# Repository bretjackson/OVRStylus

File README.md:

# OVR Stylus

The OVR Stylus is an open-source software/hardware design for a 3D input stylus used in virtual and augmented reality applications. With a touch pad, two input buttons, LRA-based vibrotactile haptic feedback, and Bluetooth communication, the 3D-printed prop’s light-weight design (35g) enables creative and precise interaction.

A paper describing the implementation was published at the [Workshop on Novel Input Devices and Interaction Techniques](https://sites.google.com/view/nidit) at the IEEE Virtual Reality 2020 conference. 

This repository archives the files needed to create your own OVR Stylus or to create a modified design.

## Repository Contents

* **/Case** - 3D printing files for the stylus case (.stl, Fusion 360 .f3z)
* **/Documentation** - A copy of the NIDIT paper (.pdf)
* **/Firmware** - Arduino  code used in the stylus and central device
* **/Hardware** - Eagle design files, BOM, Gerber files (.brd, .sch, etc.)
* **/VRPN** - Patch file and stylus classes to integrate with the [VRPN library](https://github.com/vrpn/vrpn)

### Hardware Manufacture

#### PCB

The hardware directory contains the design files needed to print the custom circuit board. The gerber files can be uploaded directly to manufactures (e.g. [Seeed Fusion Studio](https://www.seeedstudio.com/fusion.html)). Ordering specifications including board thickness and other properties are listed in the `PCB Specs - Ordering Info` file. The component placement list and assembly drawing can be used for pick-n-place machines if using professional assembly.

To modify the design the Autodesk Eagle design files for the schematic and board layout are also included.

#### Haptic Controller

The design uses the Fyber Labs [LRA Haptic Flex Module](https://www.tindie.com/products/fyberlabs/lra-haptic-flex-module/). A Samsung 8mm LRA motor can be purchased from the same website. Solder the motor leads to the +0 and -0 through-hole pads. Connect the PWM pad to the stylus's P3 pad. The VIN, GND, SDA, and SCL pads can be connected to the respective pads on the stylus. I recommend using 28 gauge stranded wire and making the leads very short. The haptic flex module is placed vertically at the button end of the stylus. 

#### Sliding Touch Sensor

To capture sliding touch input, a [Spectra Symbol 50mm Linear ThinPot poteniometer](https://www.amazon.com/SPECTRA-SYMBOLLINEAR-THINPOT-50-MM/dp/B005T844FU) is mounted in the groove in the top of the case. Solder leads to the potentiometer pins as described [here](https://learn.sparkfun.com/tutorials/softpot-hookup-guide/all). The 3V3 and GND leads can be kept shorter and be soldered to their respective pads on the stylus pcb near the RX and TX pads. The analog output tab's lead should be kept longer and soldered to the P4 pad at the front of the stylus (It will need to route behind the battery's JST connector). This P4 pad already contains a buildin 10kΩ resistor between the pad and ground that pulls the SoftPot's analog output signal down.

Once the soldering is complete, the potentimeter can be slide sideways into the groove in the top of the stylus case and the adhesive backing can be removed to secure it in place.

#### Battery

The case is designed to fit a [Sparkfun 110mAh Lithium ion battery](https://www.sparkfun.com/products/13853). The battery is mounted in the case underneath the PCB. The wires can either be routed to the front of the PCB and around the buttons to connect to the JST connector, or through the second large hole in the PCB.
    
### 3D Printed Case

The Case folder contains the STL files for the case. Multiple optical tracking end caps are included if multiple styluses will be made for use with the same optical tracking system.

For the prototype, the files were printed with a Makerbot Replicator 5th gen, although more professional results can be obtained with a higher quality resin printer. The prints were made with the standard settings in Makerbot Print, using support material. The top and bottom are designed to fit oriented vertically on the build platform. The support material will need to be removed with a razor blade. The button file will need to be printed twice for the two buttons.

The threading for both endcaps is ISO metric M14x2 profile. Depending on the quality of your printer, the threads may need to be cleaned up using a corresponding bolt and nut. Run the bolt a few times into the endcap to remove any extra plastic from the 3D printing.

The bottom component contains an ANSI 4-40 UNC threaded hole in the center support. This hole may also need the threads to be cleaned up using a steel bolt.

To assemble the components, mount the battery in the slot in the stylus bottom. Route the wires around the center support to the front of the stylus and the top of the board. The haptic module should sit vertically in the  space at the front. The LRA can be hot glued in the smaller slot at the front (The tabs may need to be bent slightly to clear the top of the case). The PCB can be screwed to the center support with a 1/4 inch 4-40 bolt. Place the 3D printed buttons so that they protrude from the top of the stylus, and snap the top and bottom together, making sure the buttons remain in place.  Screw on the end caps.

If the case needs to be modified, the Autodesk Fusion 360 design files are included in the Case directory.

### Software

The following section outlines the software requirements for both the stylus and the central device connected to the host computer.

#### Stylus Software

The stylus code is written for the Arduino environment. Download and install the [Arduino IDE](https://www.arduino.cc/en/Main/Software). The main stylus code is found in Firmware/Stylus.ino. To get started, open the file in the Arduino IDE.

To begin controling the LRA Haptic flex chip, you will need to install the Adafruit_DRV2605 Library. You can do that by going to the Arduino library manager under Sketch -> Include Library -> Manage Libraries... Then search for DRV2605 and find the Adafruit DRV2605 Library and click Install.

The stylus code uses the Pfod low-power Arduino Library by Mathew Ford. A tutorial for installing this software can be found [here](https://www.forward.com.au/pfod/BLE/LowPower/index.html). Below, we copy the most pertinent steps for archival purposes. 

Install [Sandeep Minstry's nRF5 library](https://github.com/sandeepmistry/arduino-nRF5):
1. Go into File → Preferences
2. Add `https://sandeepmistry.github.io/arduino-nRF5/package_nRF5_boards_index.json` as an "Additional Board Manager URL"
3. Open the Boards Manager from the Tools -> Board menu and install "Nordic Semiconductor nRF5 Boards".

Add the nRF5 Flash Softdevice tool:
1. In a terminal, cd <SKETCHBOOK>, where <SKETCHBOOK> is your Arduino Sketch folder:
OS X: ~/Documents/Arduino
Linux: ~/Arduino
Windows: ~/Documents/Arduino
2. Create the following directories: tools/nRF5FlashSoftDevice/tool/
3. Download nRF5FlashSoftDevice.jar to <SKETCHBOOK>/tools/nRF5FlashSoftDevice/tool/ (a local copy of nRF5FlashSoftDevice.jar is here)
4. Restart the Arduino IDE

Install the pfod_lp_nrf52 hardware support.
1. Download the [pfod_lp_nrf52.zip](https://www.forward.com.au/pfod/BLE/LowPower/pfod_lp_nrf52.zip) file. (A local copy can also be found in the Firmware directory.)
2. Start the Arduino IDE, Open the File → Preferences window an at the bottom find the directory where the preferences.txt file is stored. In Window's 7 you can click on that path to open the directory in the Explorer.
3. From the preferences.txt directory, open the packages sub-directory and then the sandeepmistry sub-directory which contains the hardware and tools directories.
4. Delete the hardware directory.
5. Unzip pfod_lp_nrf52.zip to the sandeepmistry directory to install the pfod low power support. This will install the modified hardware directory.
6. Close and restart the Arduino IDE.
7. Open the Tools → Board and scroll down to find the pfod low power nRF52832 boards.
8. Select the `*Redbear BLE Nano 2` board.
9. Under the Tools menu, make sure the programmer is set to `CMSIS-DAP`.

To Program the board, we use a [Particle Debugger](https://store.particle.io/products/particle-debugger). Connect the debugger's GND, SCLK, and SDIO pins to the corresponding pins at the front of the stylus PCB. If you intend to debug frequently, placing Pogo pins in a breadboard allow you to temporarly create connections with the stylus pcb easily without soldering.

Power the stylus pcb and then plug the particle debugger into a usb port on the programming computer. In the tools menu, make sure the usb is selected as the port.

Before the program can be loaded a Nordic Softdevice must be uploaded to the board. Select the `nRF52 Flash SoftDevice` option half way down the Tools menu. The project uses the S132 version 2.0.1 soft device. It is already included with the Sandeep Minstry package.

Once the flash is complete, upload the Stylus sketch onto the stylus pcb.

#### Host Central Device

Multiple BLE-supporting hardware can be used to connect with the stylus. Our implementation uses a stock [Arduino Nano 33 BLE](https://store.arduino.cc/usa/nano-33-ble) module to serve as a BLE to serial repeater. 

Load the Software:
1. Open the Boards Manager from the Tools -> Board menu and install "Arduino nRF528x Boards (Mbed OS)".
2. Select  `Arduino Nano 33 BLE` as the current board and make sure the port corresponds with the USB connection.
3. Upload the nano33_central.ino from the Firmware Directory to the Nano board.

#### VRPN

The VRPN directory contains a patch file to add the OVR Stylus files to the [VRPN library](https://github.com/vrpn/vrpn). The patch was made against commit: 3863b1e089b3070ae37e25fa4a85ab3bb138ee12

After cloning the vrpn library, apply the patch:
```
git apply vrpn_ovrstylus_changes.patch
```

The Stylus device files are also included in the VRPN directory if you would like to manually apply them.

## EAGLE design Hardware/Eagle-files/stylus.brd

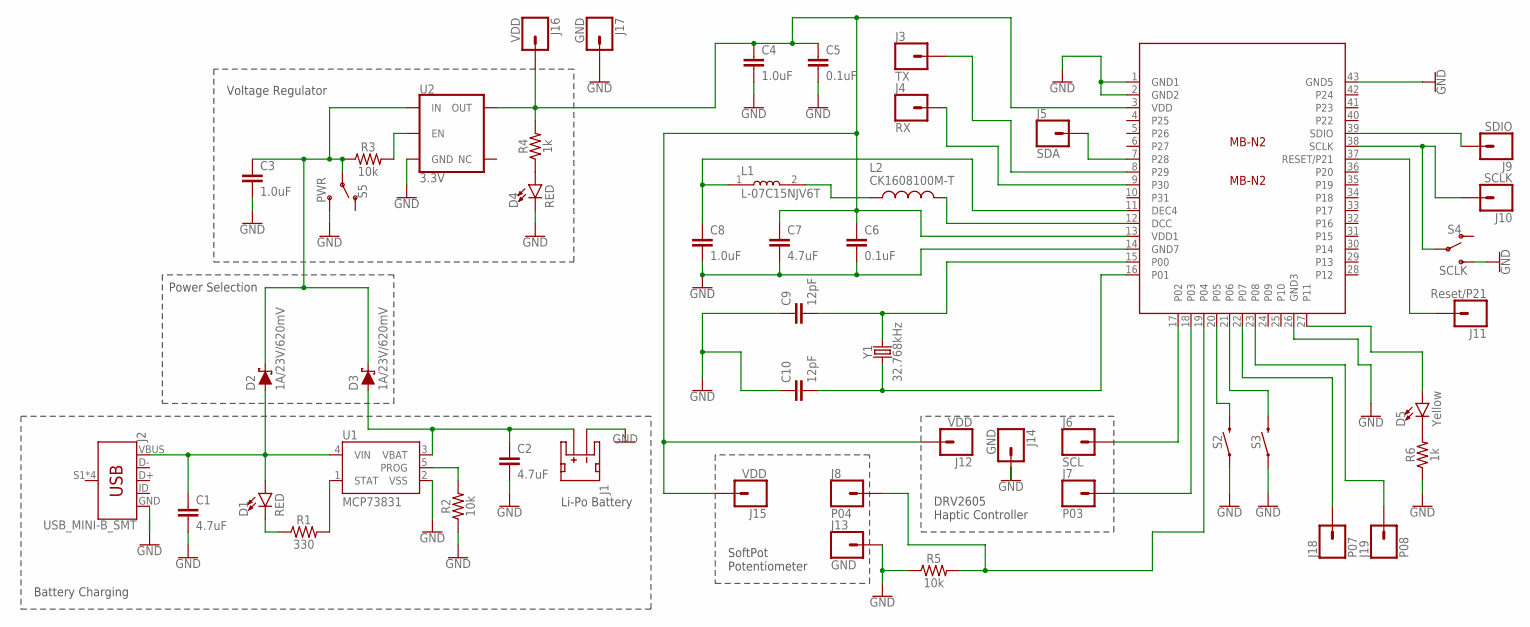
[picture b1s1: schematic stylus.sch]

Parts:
C1, C2, C7: 4.7uF; 0603
C3, C4, C8: 1.0uF; 0603
C5, C6: 0.1uF; 0603
C9, C10: 12pF; 0603
D1: RED; LED-1206
D2, D3: 1A/23V/620mV; SOD-323
D4: RED; LED-0603
D5: Yellow; LED-1206
J1: LIPO Bat; JST-2-SMD
J2: USB_MINI-B_SMT; USB-MINIB
J3: TX; 1X01
J4: RX; 1X01
J5: SDA; 1X01
J6: SCL; 1X01
J7: P03; 1X01
J8: P04; 1X01
J9: SDIO; 1X01
J10: SCLK; 1X01
J11: Reset/P21; 1X01
J12, J15, J16: VDD; 1X01
J13, J14, J17: GND; 1X01
J18: P07; 1X01
J19: P08; 1X01
L1: L-07C15NJV6T; INDC1005X60N
L2: CK1608100M-T; INDC1608X95N
MB-N2: MB-N2
R1: 330; 0603
R2, R3, R5: 10k; 0603
R4, R6: 1k; 0603
S2, S3: MOMENTARY-SWITCH-SPST-SMD-4.5MM; TACTILE_SWITCH_SMD_4.5MM
S4: SCLK; SWITCH_DPDT_SMD_AYZ0202
S5: PWR; SWITCH_SPST_SMD_A
U1: MCP73831; SOT23-5
U2: 3.3V; SOT23-5
Y1: 32.768kHz; CRYSTAL-SMD-3.2X1.5MM

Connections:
DCC: L2.2, MB-N2.12 (DCC)
DEC4: C8.1, L1.1, MB-N2.11 (DEC4)
EN: R3.2, U2.3 (EN)
GND: C1.2, C2.2, C3.2, C4.2, C5.2, C6.2, C7.2, C8.2, C9.1, C10.1, D4.C, J1.1 (-), J2.GND, J13.1, J14.1, J17.1, MB-N2.1 (GND1), MB-N2.2 (GND2), MB-N2.14 (GND7), MB-N2.26 (GND3), MB-N2.43 (GND5), R2.1, R5.1, R6.1, S2.2 (1), S2.3 (1), S3.2 (1), S3.3 (1), S4.3 (S), S5.3 (S), U1.2 (VSS), U2.2 (GND)
unnamed: D1.C, R1.1
unnamed: D4.A, R4.1
unnamed: L1.2, L2.1
unnamed: C9.2, MB-N2.15 (P00), Y1.P$2 (2)
unnamed: C10.2, MB-N2.16 (P01), Y1.P$1 (1)
unnamed: J11.1, MB-N2.37 (RESET/P21)
unnamed: D5.A, MB-N2.27 (P11)
unnamed: D5.C, R6.2
P03: J7.1, MB-N2.18 (P03)
P04: J8.1, MB-N2.19 (P04), R5.2
P05: MB-N2.20 (P05), S2.1 (2), S2.4 (2)
P06: MB-N2.21 (P06), S3.1 (2), S3.4 (2)
P07: J18.1, MB-N2.22 (P07)
P08: J19.1, MB-N2.23 (P08)
PROG: R2.2, U1.5 (PROG)
RX: J4.1, MB-N2.9 (P30)
SCL: J6.1, MB-N2.17 (P02)
SCLK: J10.1, MB-N2.38 (SCLK), S4.2
SDA: J5.1, MB-N2.7 (P28)
SDIO: J9.1, MB-N2.39 (SDIO)
STAT: R1.2, U1.1 (STAT)
TX: J3.1, MB-N2.8 (P29)
VBAT: C2.1, D3.A, J1.2 (+), U1.3 (VBAT)
VDD: C4.1, C5.1, C6.1, C7.1, J12.1, J15.1, J16.1, MB-N2.3 (VDD), MB-N2.13 (VDD1), R4.2, U2.5 (OUT)
VIN: C1.1, D1.A, D2.A, J2.VBUS, U1.4 (VIN)
VR-IN: C3.1, D2.C, D3.C, R3.1, S5.2, U2.1 (IN)

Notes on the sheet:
Power Selection
DRV2605 Haptic Controller
SoftPot Potentiometer
Li-Po Battery
Voltage Regulator
Battery Charging

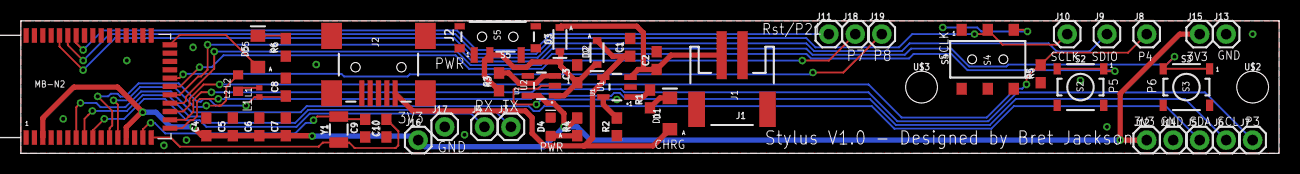
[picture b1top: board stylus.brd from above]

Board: 2 copper layers, 120.7 x 12.7 mm, 52 parts (0 on the bottom side), 30 nets.

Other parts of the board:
U$2, U$3: STAND-OFF-TIGHT

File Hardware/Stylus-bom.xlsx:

Ref Des | MP | Quantity | DIGI-KEY_PURCHASE_URL | MF | DIGI-KEY_PART_NUMBER | Description
C1, C2, C7 | CL10A475MQ8NNNC | 3 | https://www.digikey.com/product-detail/en/samsung-electro-me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 | Samsung | 1276-1907-1-ND | 4.7 µF ceramic capacitor 20% 6.3V X5R 0603
C3, C4, C8 | CL10A105KO8NNNC | 3 | https://www.digikey.com/product-detail/en/samsung-electro-me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 | Samsung | 1276-1034-1-ND | 1µF ±10% 16V Ceramic Capacitor X5R 0603
C5, C6 | CL10B104KB8NNNL | 2 | https://www.digikey.com/product-detail/en/samsung-electro-me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 | Samsung | 1276-CL10B104KB8NNNLCT-ND | 0.1µF ±10% 50V Ceramic Capacitor X7R 0603
C9, C10 | CL10C120JB8NNNC | 2 | https://www.digikey.com/product-detail/en/samsung-electro-me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 | Samsung | 1276-1254-1-ND | 12pF ±5% 50V Ceramic Capacitor C0G, NP0 0603
D1 | LTST-C150KRKT | 1 | https://www.digikey.com/product-detail/en/lite-on-inc/LTST-C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 | Lite-On Inc. | 160-1405-1-ND | LED RED CLEAR 1206 SMD
D2, D3 | BAT20JFILM | 2 | https://www.digikey.com/product-detail/en/BAT20JFILM/497-338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 | STMicroelectronics | 497-3381-1-ND | Diode Schottky 23V 1A Surface Mount SOD-323
D4 | 5988010107F | 1 | https://www.digikey.com/product-detail/en/dialight/598801010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 | Dialight | 350-2029-1-ND | LED RED CLEAR 0603 SMD
D5 | LTST-C150KSKT | 1 | https://www.digikey.com/product-detail/en/lite-on-inc/LTST-C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 | Lite-On Inc. | 160-1406-1-ND | LED YELLOW CLEAR 1206 SMD
J1 | S2B-PH-SM4-TB(LF)(SN) | 1 | https://www.digikey.com/product-detail/en/jst-sales-america-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 | JST Sales America Inc. | 455-1749-1-ND | JST CONN HEADER SMD R/A 2POS 2MM
J2 | MUSB-05-F-B-SM-A-K-TR | 1 | https://www.digikey.com/product-detail/en/samtec-inc/MUSB-05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 | Samtec Inc. | SAM13208CT-ND | USB type Mini-B Connector
L1 | L-07C15NJV6T | 1 | https://www.digikey.com/product-detail/en/johanson-technolog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 | Johanson Technology | 712-1408-1-ND | Inductor RF Chip Multi-Layer 15nH 5% 100MHz 8Q-Factor Ceramic 250mA 600mOhm DCR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
L2 | CK1608100M-T | 1 | https://www.digikey.com/product-detail/en/taiyo-yuden/CK1608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 | Taiyo Yuden | 587-1684-1-ND | INDUCTOR, 10UH, 50mA, 20%, 17MHZ, SMD
R1 | ERA-3AEB331V | 1 | https://www.digikey.com/product-detail/en/panasonic-electron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 | Panasonic | P330DBCT-ND | 330 Ohms ±0.1% 0.1W, 1/10W Chip Resistor 0603
R2, R3, R5 | RR0816P-103-D | 3 | https://www.digikey.com/product-detail/en/susumu/RR0816P-103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 | Susumu | RR08P10.0KDCT-ND | 10 kOhms ±0.5% 0.063W, 1/16W Chip Resistor 0603
R4, R6 | RR0816P-102-D | 2 | https://www.digikey.com/product-detail/en/susumu/RR0816P-102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 | Susumu | RR08P1.0KDCT-ND | 1 kOhms ±0.5% 0.063W, 1/16W Chip Resistor 0603
S2, S3 | TL3315NF160Q | 2 | https://www.digikey.com/product-detail/en/e-switch/TL3315NF1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 | E-Switch | EG4621CT-ND | Momentary Switch (Pushbutton) - SPST 4.5mm
S4 | AYZ0202AGRLC | 1 | https://www.digikey.com/product-detail/en/c-k/AYZ0202AGRLC/4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 | C&K | 401-2013-1-ND | Double Pole, Double Throw (DPDT) Switch
S5 | MA12RTR | 1 | https://www.digikey.com/product-detail/en/apem-inc/MA12RTR/6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 | APEM Inc. | 679-1847-1-ND | SWITCH SLIDE SPDT 300MA 4V Right Angle
MB-N2 | MB-N2 | 1 | CUSTOMER SUPPLIED | RedBearLab/Particle | CUSTOMER SUPPLIED | Redbearlab MB-N2 ble microcontroller
U1 | MCP73831T-2ATI/OT | 1 | https://www.digikey.com/product-detail/en/microchip-technolo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 | Microchip Technology | MCP73831T-2ATI/OTCT-ND | MCP73831T Li-Ion, Li-Pol Controller
U2 | AP2112K-3.3TRG1 | 1 | https://www.digikey.com/product-detail/en/diodes-incorporate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 | Diodes Incorporated | AP2112K-3.3TRG1DICT-ND | AP2112 - 600mA CMOS LDO Regulator w/ Enable
Y1 | SC32S-12.5PF20PPM | 1 | https://www.digikey.com/product-detail/en/seiko-instruments/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 | Seiko Instruments | 728-1073-1-ND | 32.768kHz ±20ppm Crystal 12.5pF 70 kOhms 2-SMD, No Lead

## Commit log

2020-02-09 Initial files
2020-02-09 Updated readme instructions
2020-02-09 Added pictures of the stylus
2020-02-11 Added paper pdf

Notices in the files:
parts and their libraries:
SparkFun-Capacitors: Licensing: Creative Commons ShareAlike 4.0 International - https://creativecommons.org/licenses/by-sa/4.0
